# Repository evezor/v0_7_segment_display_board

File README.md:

# 7 Segment Display board
*please note this board has been deprecated.

An edge board containing qty(2), 4 charector 7 segment displays

source files can be found here: https://github.com/evezor/v0_7_segment_display_board

This board uses the Evezor Stamp STMF405 MCU

source: https://github.com/evezor/Evezor-Stamp-STMF405

Evezor® and all associated marks, logos, and designs are registered trademarks and protected by copyright. Unauthorized use or reproduction of these trademarks and copyrighted materials is strictly prohibited.

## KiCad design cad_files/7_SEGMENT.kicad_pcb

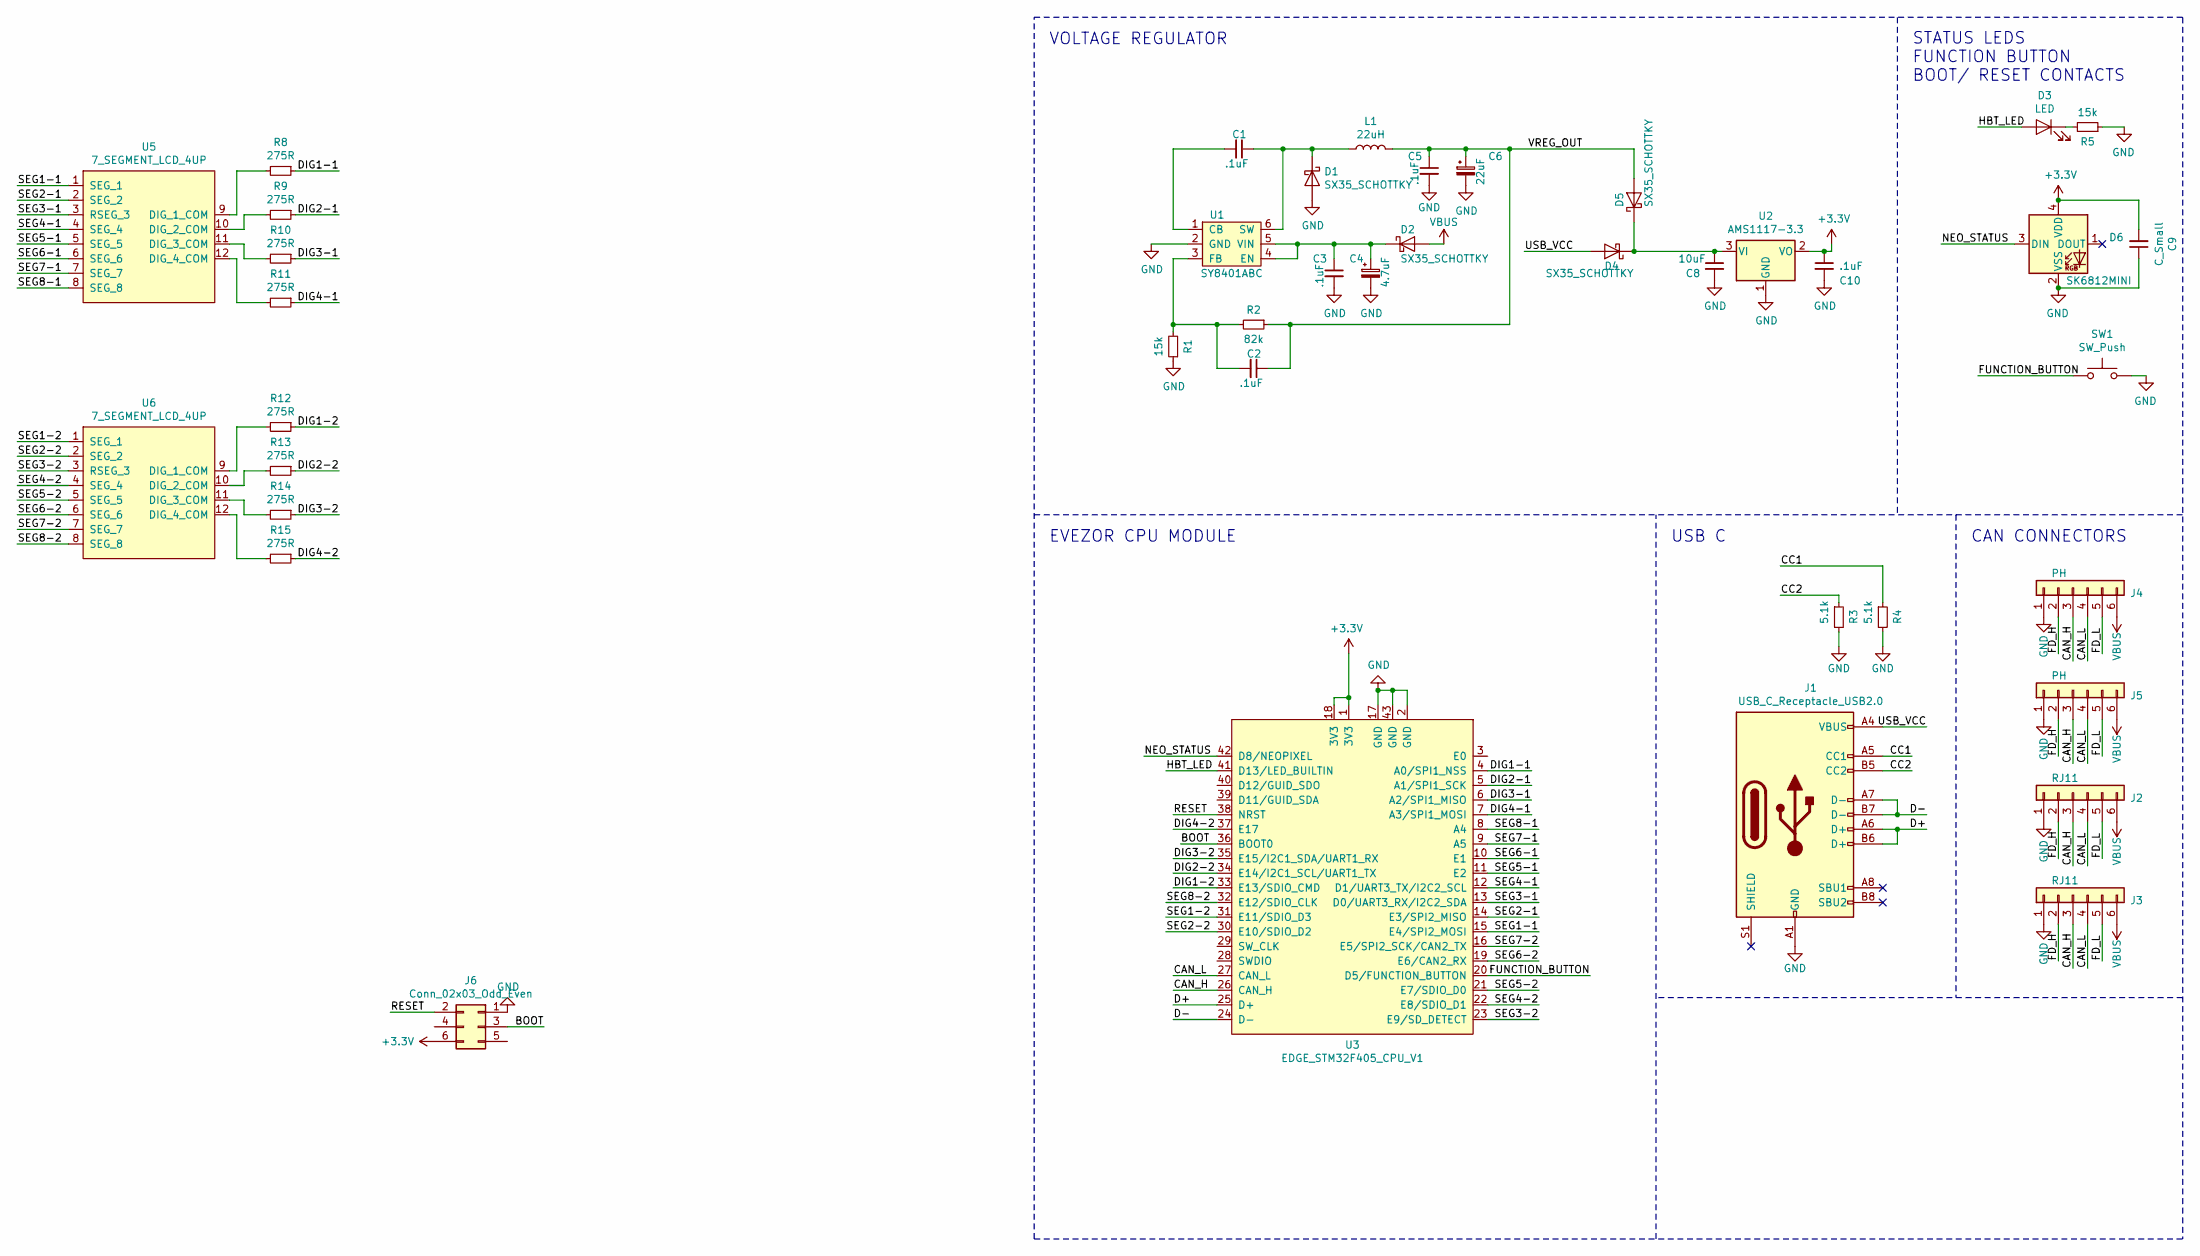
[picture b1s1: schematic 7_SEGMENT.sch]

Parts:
C1, C2, C3, C5, C10: .1uF; C_0603_1608Metric
C4: 4.7uF; C_0805_2012Metric
C6: 22uF; C_0805_2012Metric
C8: 10uF; C_0805_2012Metric
C9: C_Small; C_0603_1608Metric
D1, D2, D4, D5: SX35_SCHOTTKY; D_SMA
D3: LED; LED_0603_1608Metric
D6: SK6812MINI; LED_SK6812MINI_PLCC4_3.5x3.5mm_P1.75mm
J1: USB_C_Receptacle_USB2.0; USB_C_Receptacle_HRO_TYPE-C-31-M-12
J2, J3: RJ11; RJ11_C189747_Horizontal
J4, J5: PH; JST_PH_B6B-PH-K_1x06_P2.00mm_Vertical
J6: Conn_02x03_Odd_Even; PinSocket_2x03_P2.54mm_Vertical_SMD
L1: 22uH; INDUCTOR_7.5X6.6_GCDA0630-220MC
R1, R5: 15k; R_0603_1608Metric
R2: 82k; R_0603_1608Metric
R3, R4: 5.1k; R_0603_1608Metric
R8, R9, R10, R11, R12, R13, R14, R15: 275R; R_0603_1608Metric
SW1: SW_Push; SWITCH_2x3_SMD_TACTILE_GREEN
U1: SY8401ABC; SOT-23-6
U2: AMS1117-3.3; SOT-223-3_TabPin2
U3: EDGE_STM32F405_CPU_V1; EDGE_STAMP
U5, U6: 7_SEGMENT_LCD_4UP; 7_SEGMENT_LCD_4UP_SMD

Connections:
+3V3: C9.2, C10.1, D6.4 (VDD), J6.6, U2.2 (VO), U3.1 (3V3), U3.18 (3V3)
/BOOT: J6.3, U3.36 (BOOT0)
/CAN_H: J2.3, J3.3, J4.3, J5.3, U3.26 (CAN_H)
/CAN_L: J2.4, J3.4, J4.4, J5.4, U3.27 (CAN_L)
/CC1: J1.A5 (CC1), R4.1
/CC2: J1.B5 (CC2), R3.1
/D+: J1.A6 (D+), J1.B6 (D+), U3.25 (D+)
/D-: J1.A7 (D-), J1.B7 (D-), U3.24 (D-)
/DIG1-1: R8.1, U3.4 (A0/SPI1_NSS)
/DIG1-2: R12.1, U3.33 (E13/SDIO_CMD)
/DIG2-1: R9.1, U3.5 (A1/SPI1_SCK)
/DIG2-2: R13.1, U3.34 (E14/I2C1_SCL/UART1_TX)
/DIG3-1: R10.1, U3.6 (A2/SPI1_MISO)
/DIG3-2: R14.1, U3.35 (E15/I2C1_SDA/UART1_RX)
/DIG4-1: R11.1, U3.7 (A3/SPI1_MOSI)
/DIG4-2: R15.1, U3.37 (E17)
/FD_H: J2.2, J3.2, J4.2, J5.2
/FD_L: J2.5, J3.5, J4.5, J5.5
/FUNCTION_BUTTON: SW1.1, U3.20 (D5/FUNCTION_BUTTON)
/HBT_LED: D3.2 (A), U3.41 (D13/LED_BUILTIN)
/NEO_STATUS: D6.3 (DIN), U3.42 (D8/NEOPIXEL)
/RESET: J6.2, U3.38 (NRST)
/SEG1-1: U3.15 (E4/SPI2_MOSI), U5.1 (SEG_1)
/SEG1-2: U3.31 (E11/SDIO_D3), U6.1 (SEG_1)
/SEG2-1: U3.14 (E3/SPI2_MISO), U5.2 (SEG_2)
/SEG2-2: U3.30 (E10/SDIO_D2), U6.2 (SEG_2)
/SEG3-1: U3.13 (D0/UART3_RX/I2C2_SDA), U5.3 (RSEG_3)
/SEG3-2: U3.23 (E9/SD_DETECT), U6.3 (RSEG_3)
/SEG4-1: U3.12 (D1/UART3_TX/I2C2_SCL), U5.4 (SEG_4)
/SEG4-2: U3.22 (E8/SDIO_D1), U6.4 (SEG_4)
/SEG5-1: U3.11 (E2), U5.5 (SEG_5)
/SEG5-2: U3.21 (E7/SDIO_D0), U6.5 (SEG_5)
/SEG6-1: U3.10 (E1), U5.6 (SEG_6)
/SEG6-2: U3.19 (E6/CAN2_RX), U6.6 (SEG_6)
/SEG7-1: U3.9 (A5), U5.7 (SEG_7)
/SEG7-2: U3.16 (E5/SPI2_SCK/CAN2_TX), U6.7 (SEG_7)
/SEG8-1: U3.8 (A4), U5.8 (SEG_8)
/SEG8-2: U3.32 (E12/SDIO_CLK), U6.8 (SEG_8)
/USB_VCC: D4.2 (A), J1.A4 (VBUS), J1.A9 (VBUS), J1.B4 (VBUS), J1.B9 (VBUS)
/VREG_OUT: C2.1, C5.1, C6.1, D5.2 (A), L1.2, R2.1
GND: C3.2, C4.2, C5.2, C6.2, C8.2, C9.1, C10.2, D1.2 (A), D6.2 (VSS), J1.A1 (GND), J1.A12 (GND), J1.B1 (GND), J1.B12 (GND), J2.1, J3.1, J4.1, J5.1, J6.1, R1.1, R3.2, R4.2, R5.1, SW1.2, U1.2 (GND), U2.1 (GND), U3.2 (GND), U3.17 (GND), U3.43 (GND)
unnamed: C1.1, D1.1 (K), L1.1, U1.6 (SW)
unnamed: C1.2, U1.1 (CB)
unnamed: C2.2, R1.2, R2.2, U1.3 (FB)
unnamed: C3.1, C4.1, D2.1 (K), U1.4 (EN), U1.5 (VIN)
unnamed: C8.1, D4.1 (K), D5.1 (K), U2.3 (VI)
unnamed: D3.1 (K), R5.2
unnamed: R8.2, U5.9 (DIG_1_COM)
unnamed: R9.2, U5.10 (DIG_2_COM)
unnamed: R10.2, U5.11 (DIG_3_COM)
unnamed: R11.2, U5.12 (DIG_4_COM)
unnamed: R12.2, U6.9 (DIG_1_COM)
unnamed: R13.2, U6.10 (DIG_2_COM)
unnamed: R14.2, U6.11 (DIG_3_COM)
unnamed: R15.2, U6.12 (DIG_4_COM)
VBUS: D2.2 (A), J2.6, J3.6, J4.6, J5.6

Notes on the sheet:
EVEZOR CPU MODULE
USB C
CAN CONNECTORS
STATUS LEDS FUNCTION BUTTON BOOT/ RESET CONTACTS
VOLTAGE REGULATOR

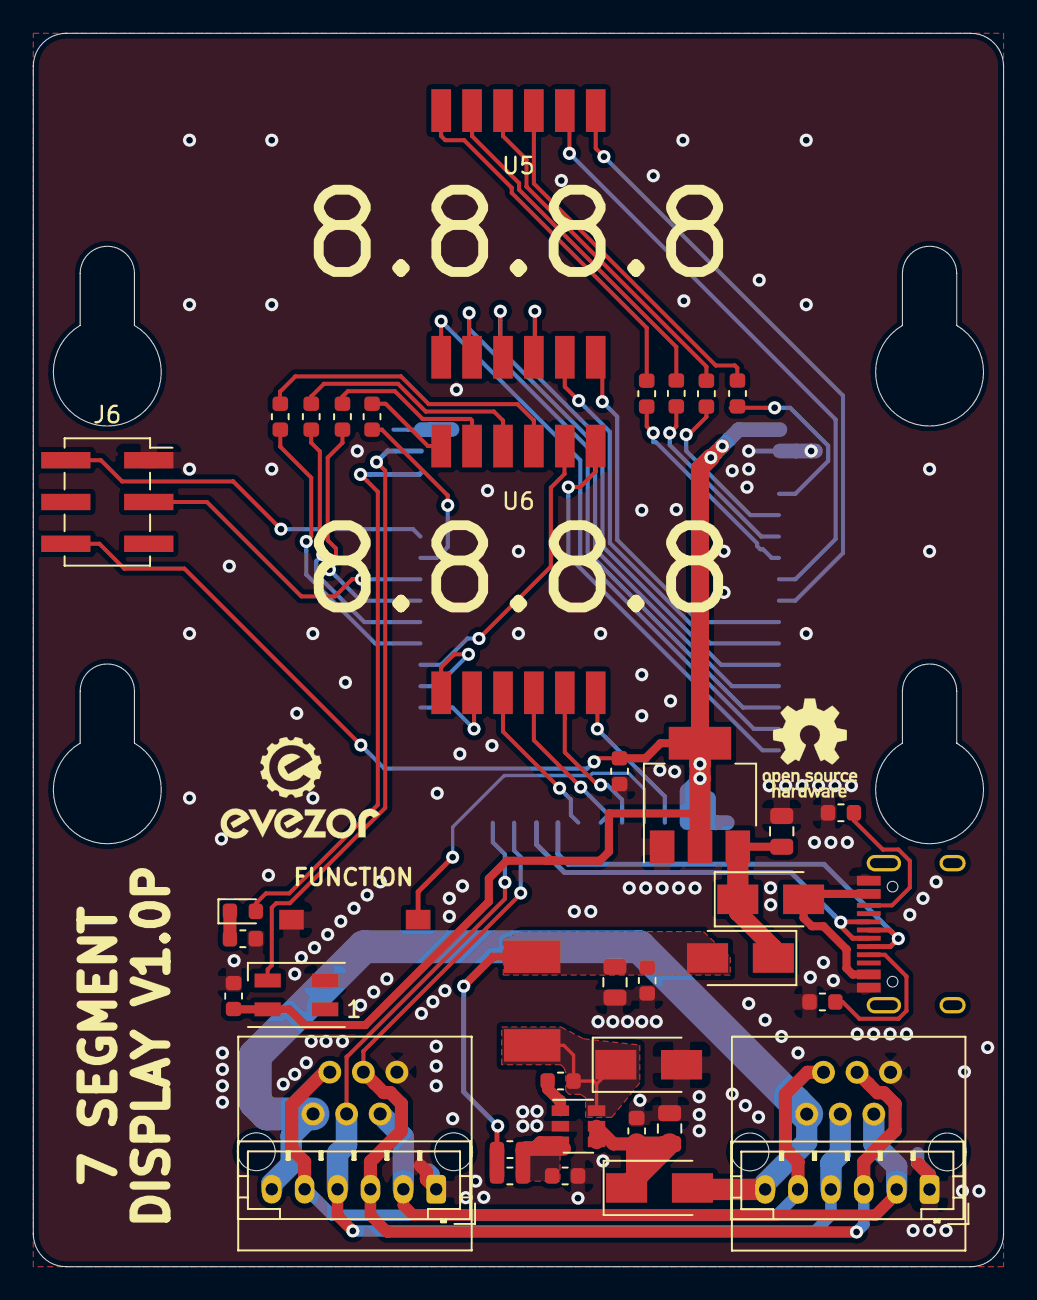
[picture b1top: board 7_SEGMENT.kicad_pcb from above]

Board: 2 copper layers, 59.0 x 75.0 mm, 41 parts (1 on the bottom side), 56 nets.

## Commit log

2020-11-08 add pin map pic
2020-11-08 add helper text
2020-11-08 move docs to docs
2020-11-08 update pin callout pics
2020-11-15 add message received animation
2023-09-11 add pics
